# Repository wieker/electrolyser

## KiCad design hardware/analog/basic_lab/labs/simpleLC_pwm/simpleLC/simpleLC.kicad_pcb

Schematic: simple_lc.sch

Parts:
C1: C; C_Disc_D3.8mm_W2.6mm_P2.50mm
D1: D; D_DO-15_P10.16mm_Horizontal
J1: Conn_01x04_Male; PinHeader_1x04_P2.54mm_Vertical
J2: Conn_01x02_Male; PinHeader_1x02_P2.54mm_Vertical
Q1: FQP27P06; TO-220-3_Vertical
R2: R; R_Axial_DIN0207_L6.3mm_D2.5mm_P2.54mm_Vertical

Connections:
+3V3: C1.1, D1.1, J1.1, J2.2
GND: C1.2, J1.4, R2.2
unnamed: D1.2, J2.1, Q1.2 (D)
unnamed: Q1.3 (S), R2.1
din: J1.2, Q1.1 (G)

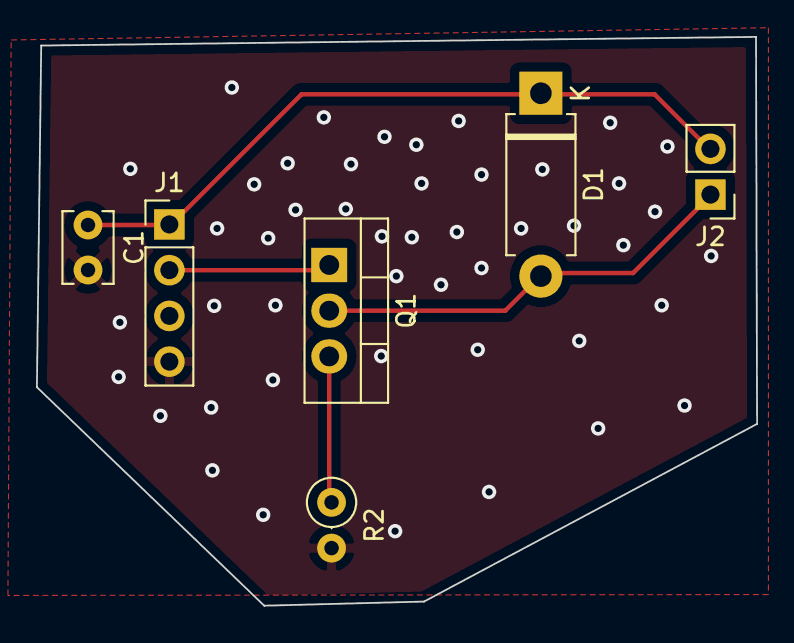
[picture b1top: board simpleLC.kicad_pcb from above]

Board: 2 copper layers, 40.0 x 31.6 mm, 6 parts (0 on the bottom side), 5 nets.

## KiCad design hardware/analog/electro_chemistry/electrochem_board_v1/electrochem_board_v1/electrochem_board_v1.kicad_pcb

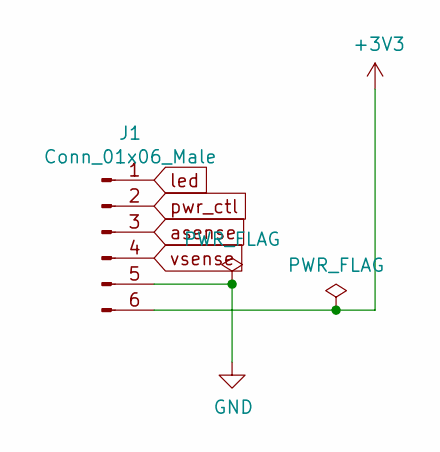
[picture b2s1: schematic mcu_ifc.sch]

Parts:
J1: Conn_01x06_Male; PinSocket_1x06_P2.54mm_Vertical

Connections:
GND: J1.5; also elsewhere on the board
asense: J1.3; also elsewhere on the board
led: J1.1; also elsewhere on the board
pwr_ctl: J1.2; also elsewhere on the board
vsense: J1.4; also elsewhere on the board

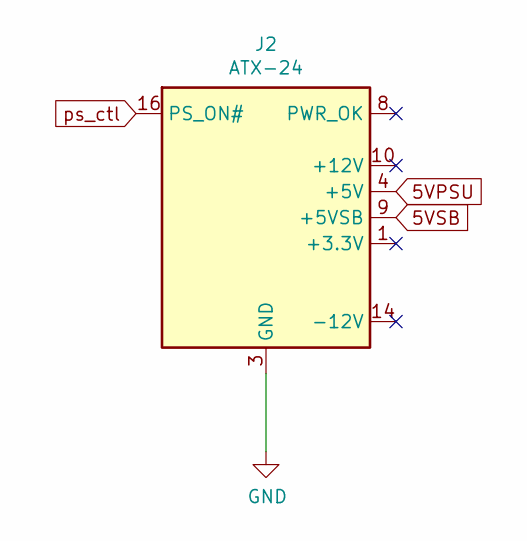
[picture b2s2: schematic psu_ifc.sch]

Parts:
J2: ATX-24; Molex_Mini-Fit_Jr_5566-24A_2x12_P4.20mm_Vertical

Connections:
5VPSU: J2.4 (+5V), J2.6 (+5V), J2.21 (+5V), J2.22 (+5V), J2.23 (+5V); also elsewhere on the board
5VSB: J2.9 (+5VSB); also elsewhere on the board
GND: J2.3 (GND), J2.5 (GND), J2.7 (GND), J2.15 (GND), J2.17 (GND), J2.18 (GND), J2.19 (GND), J2.24 (GND); also elsewhere on the board
unnamed: J2.1 (+3.3V), J2.2 (+3.3V), J2.12 (+3.3V), J2.13 (+3.3V)
unnamed: J2.10 (+12V), J2.11 (+12V)
ps_ctl: J2.16 (PS_ON#); also elsewhere on the board

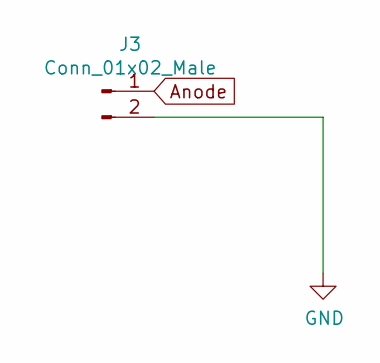
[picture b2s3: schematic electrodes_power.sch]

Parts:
J3: Conn_01x02_Male; SolderWire-1.5sqmm_1x02_P6mm_D1.7mm_OD3mm

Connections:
Anode: J3.1; also elsewhere on the board
GND: J3.2; also elsewhere on the board

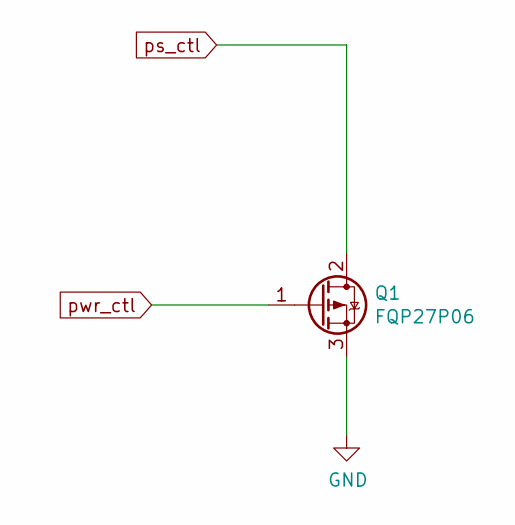
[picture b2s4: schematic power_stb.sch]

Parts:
Q1: FQP27P06; TO-220-3_Vertical

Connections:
GND: Q1.3 (S); also elsewhere on the board
ps_ctl: Q1.2 (D); also elsewhere on the board
pwr_ctl: Q1.1 (G); also elsewhere on the board

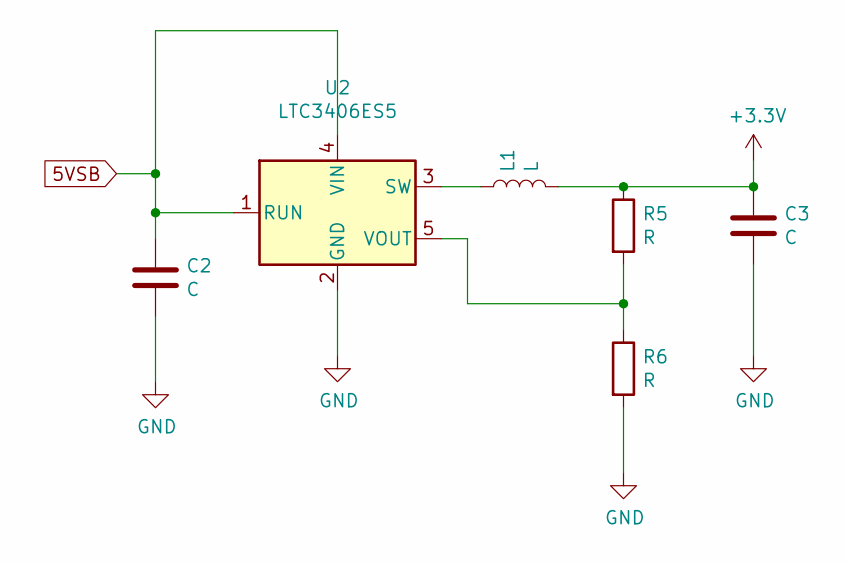
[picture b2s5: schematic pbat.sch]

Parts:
C2: C; C_0402_1005Metric
C3: C; C_0603_1608Metric
L1: L; L_1210_3225Metric
R5, R6: R; R_0402_1005Metric
U2: LTC3406ES5; TSOT-23-5

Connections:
5VSB: C2.1, U2.1 (RUN), U2.4 (VIN); also elsewhere on the board
GND: C2.2, C3.2, R6.2, U2.2 (GND); also elsewhere on the board
unnamed: L1.1, U2.3 (SW)
unnamed: R5.2, R6.1, U2.5 (VOUT)

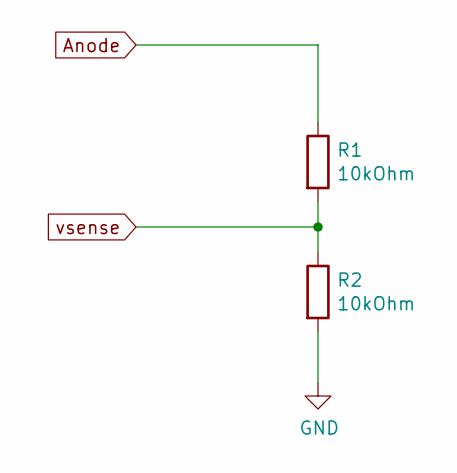
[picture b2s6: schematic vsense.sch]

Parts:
R1, R2: 10kOhm; R_0402_1005Metric

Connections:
Anode: R1.1; also elsewhere on the board
GND: R2.2; also elsewhere on the board
vsense: R1.2, R2.1; also elsewhere on the board

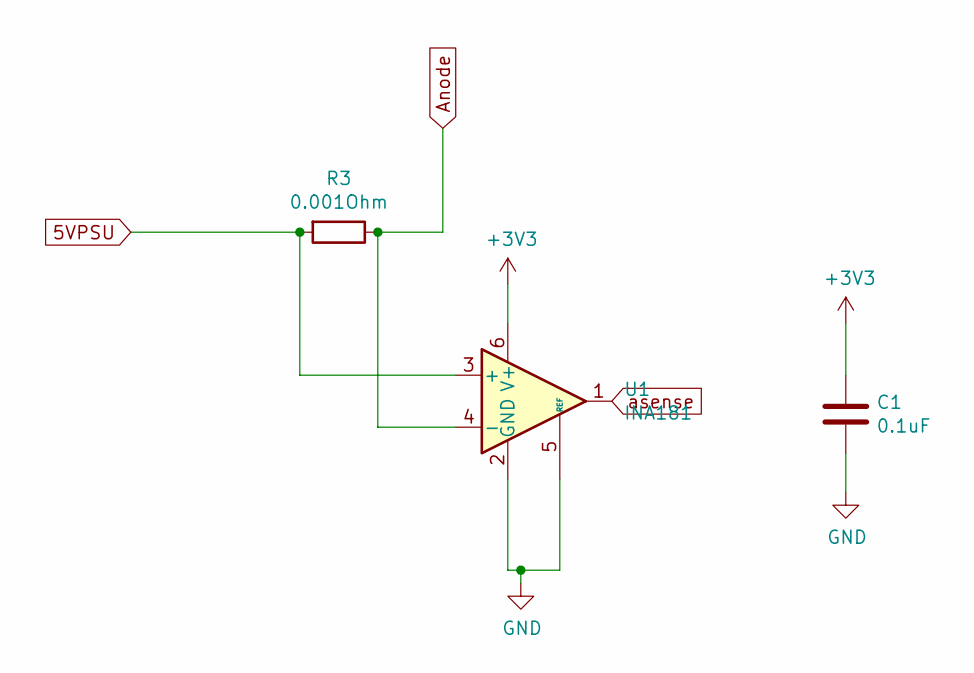
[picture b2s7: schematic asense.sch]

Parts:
C1: 0.1uF; C_0402_1005Metric
R3: 0.001Ohm; R_1206_3216Metric
U1: INA181; SOT-23-6

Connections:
5VPSU: R3.2, U1.3 (+); also elsewhere on the board
Anode: R3.1, U1.4 (-); also elsewhere on the board
GND: C1.2, U1.2 (GND), U1.5 (REF); also elsewhere on the board
asense: U1.1; also elsewhere on the board

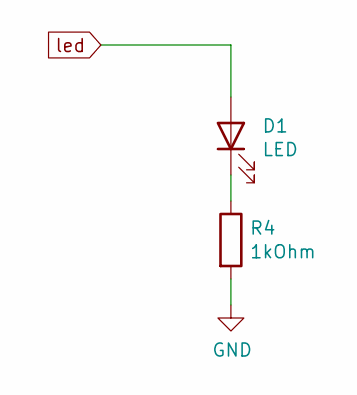
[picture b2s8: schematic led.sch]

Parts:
D1: LED; LED_1206_3216Metric
R4: 1kOhm; R_0402_1005Metric

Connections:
GND: R4.2; also elsewhere on the board
unnamed: D1.1 (K), R4.1
led: D1.2 (A); also elsewhere on the board

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
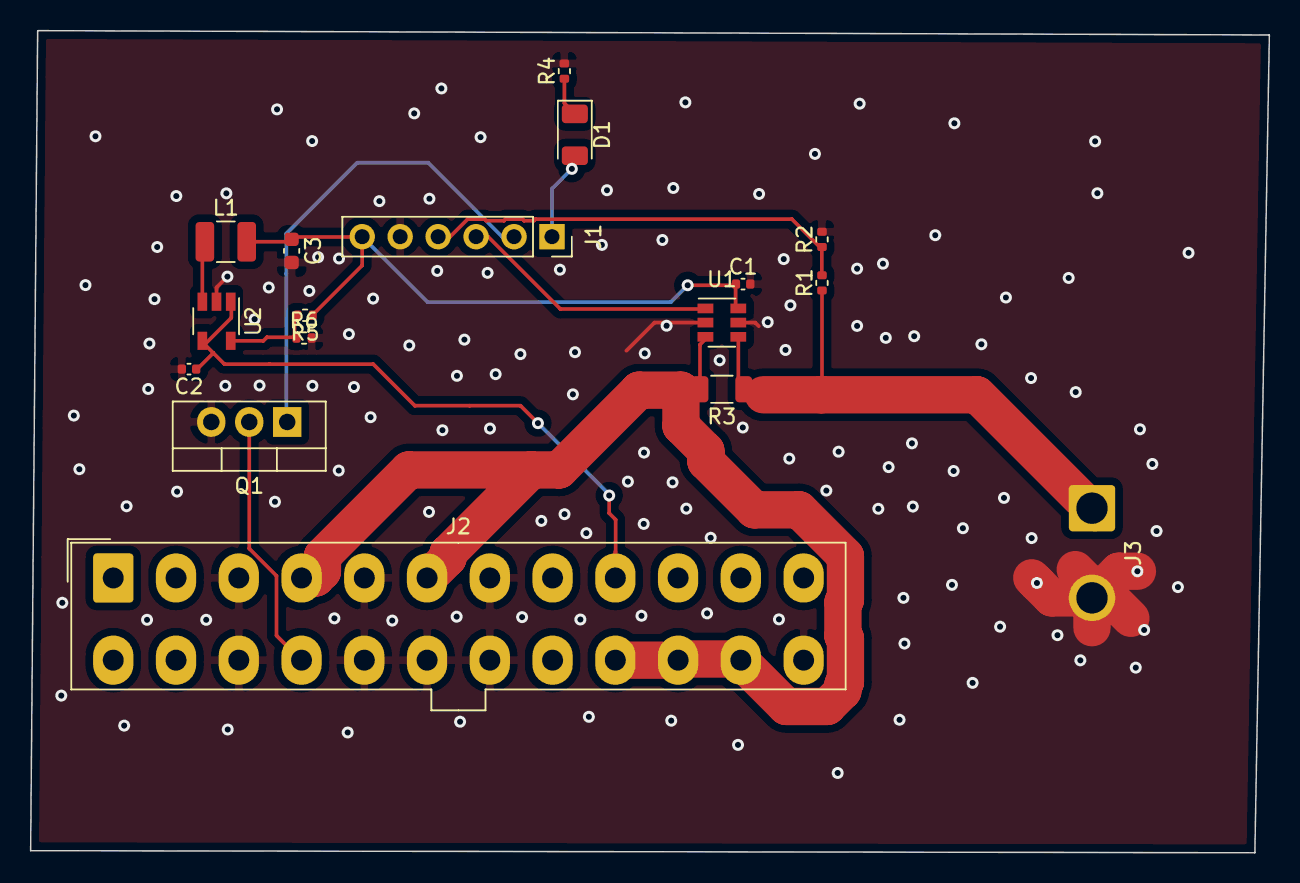
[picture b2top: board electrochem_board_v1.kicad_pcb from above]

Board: 2 copper layers, 82.9 x 55.0 mm, 17 parts (0 on the bottom side), 15 nets.

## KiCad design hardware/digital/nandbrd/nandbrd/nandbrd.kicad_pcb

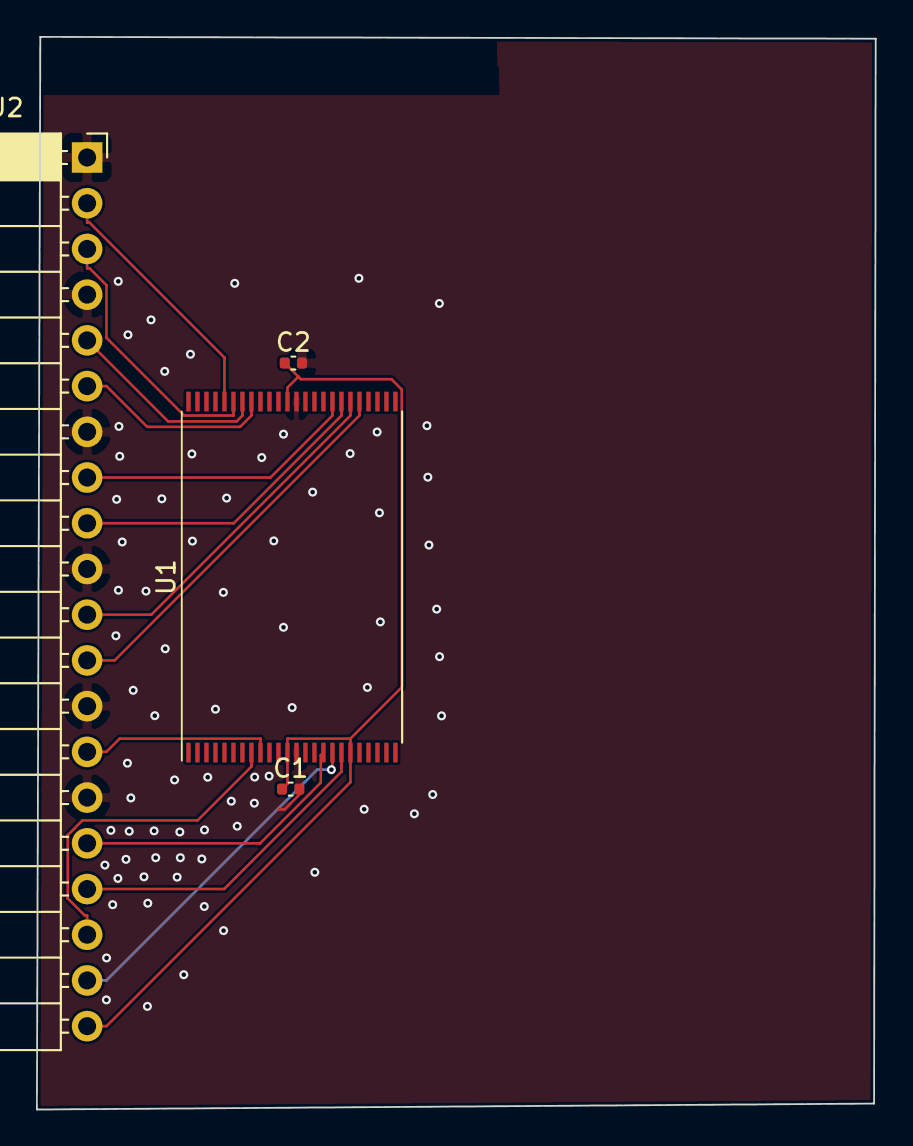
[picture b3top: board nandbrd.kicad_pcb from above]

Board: 2 copper layers, 46.6 x 59.6 mm, 4 parts (0 on the bottom side), 15 nets.

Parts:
C1: 0.1uF; C_0402_1005Metric
C2: 4.7uF; C_0402_1005Metric
J2: Conn_01x20_Male; PinSocket_1x20_P2.54mm_Horizontal
U1: MT29F1G08ABAEAWP; TSOP-I-48_18.4x12mm_P0.5mm

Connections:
ALE: J2.19, U1.17
CE: J2.14, U1.9
CLE: J2.16, U1.16
D0: J2.12, U1.29
D1: J2.11, U1.30
D2: J2.9, U1.31
D3: J2.8, U1.32
D4: J2.6, U1.41
D5: J2.5, U1.42
D6: J2.3, U1.43
D7: J2.2, U1.44
GND: C1.2, C2.2, J2.1, J2.4, J2.7, J2.10, J2.13, J2.15, U1.13, U1.36
RE: J2.18, U1.8
WE: J2.17, U1.18
WP: C1.1, C2.1, J2.20, U1.12, U1.19, U1.37

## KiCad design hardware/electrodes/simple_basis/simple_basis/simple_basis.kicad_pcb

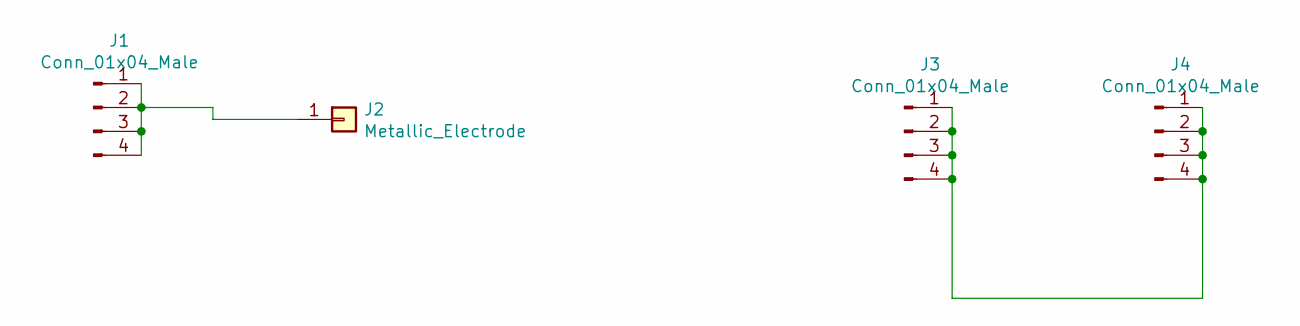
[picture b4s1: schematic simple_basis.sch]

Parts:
J1, J3, J4: Conn_01x04_Male; PinHeader_1x04_P2.54mm_Vertical
J2: Metallic_Electrode; Electrode_ThroughHole_V0.1

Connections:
unnamed: J1.1, J1.2, J1.3, J1.4, J2.1
unnamed: J3.1, J3.2, J3.3, J3.4, J4.1, J4.2, J4.3, J4.4

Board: 2 copper layers, 4 parts (0 on the bottom side), 2 nets, no tracks yet.

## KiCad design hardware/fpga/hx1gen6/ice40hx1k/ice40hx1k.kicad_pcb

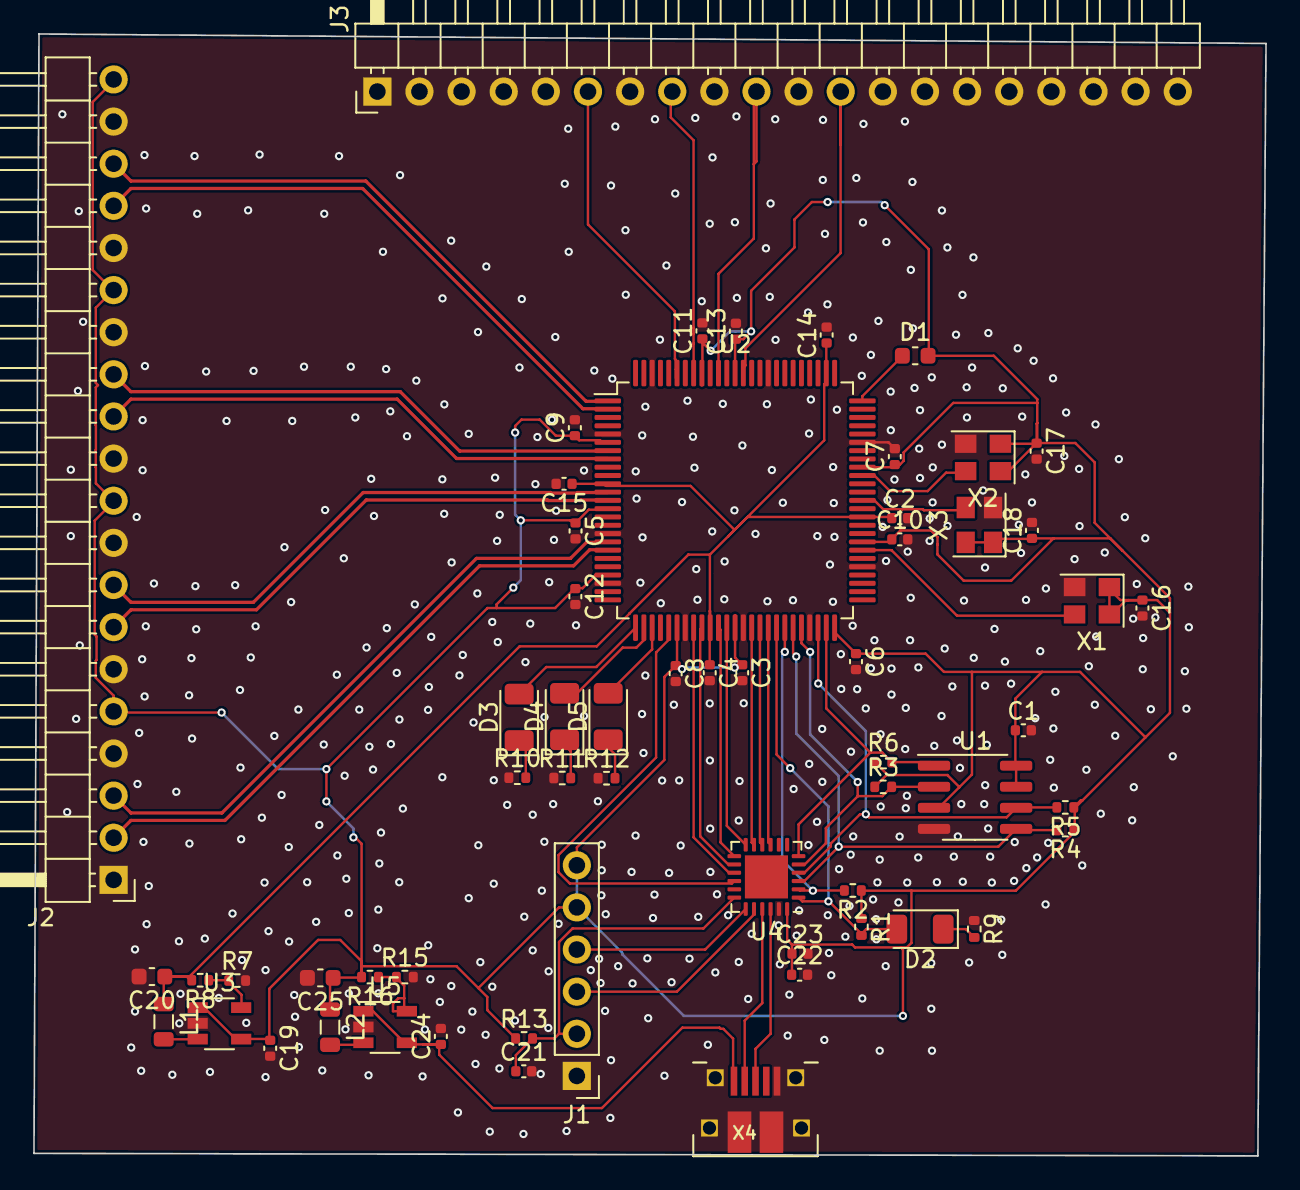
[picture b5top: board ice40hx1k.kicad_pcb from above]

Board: 2 copper layers, 74.3 x 67.6 mm, 59 parts (0 on the bottom side), 50 nets.

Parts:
C1, C2, C3, C4, C5, C6, C7, C8, C9, C10, C11, C12, C13, C14, C15, C21, C23: 0.1uF; C_0402_1005Metric
C16, C17, C18: 0.01uF; C_0402_1005Metric
C19, C22, C24: 4.7uF; C_0402_1005Metric
C20, C25: 10uF; C_0603_1608Metric
D1: CDBU05; C_0603_1608Metric
D2, D3, D4, D5: LED; LED_1206_3216Metric
J1: Conn_01x06_Male; PinHeader_1x06_P2.54mm_Vertical
J2, J3: Conn_01x20_Male; PinHeader_1x20_P2.54mm_Horizontal
L1, L2: 2.2uH; L_0805_2012Metric
R1, R2, R3, R4, R5, R6, R13: 10kOhm; R_0402_1005Metric
R7, R8, R15: 100kOhm; R_0402_1005Metric
R9, R10, R11, R12: 10kohm; R_0402_1005Metric
R16: 450kOhm; R_0402_1005Metric
U1: AT25SF081-SSHD-X; SOIC-8_3.9x4.9mm_P1.27mm
U2: ICE40HX1K-VQ100(VQFP100); LQFP-100_14x14mm_P0.5mm
U3, U5: LTC3406ES5; TSOT-23-5
U4: ATSAMD11D14A-M; QFN-24-1EP_4x4mm_P0.5mm_EP2.6x2.6mm
X1, X2, X3: ASE-10MHz; Oscillator_SMD_Abracon_ASE-4Pin_3.2x2.5mm
X4: USBFCI_10103594_MILL; FCI_10103594_MILL

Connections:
+1V2: C2.1, C4.1, C14.1, C15.1, C20.1, L1.1, R8.2, U2.11, U2.35, U2.61, U2.77
+3V3: C1.1, C3.1, C5.1, C6.1, C7.1, C8.1, C9.1, C10.1, C11.1, C12.1, C13.1, C16.1, C17.1, C18.1, C19.1, C22.1, C23.1, C25.1, D1.2, J1.5, J1.6, J2.5, J2.10, J2.15, J2.20, L2.1, R1.1, R2.1, R3.1, R4.1, R5.1, R6.1, R13.1, R16.2, U1.3, U1.7, U1.8, U2.6, U2.14, U2.22, U2.31, U2.38, U2.50, U2.58, U2.67, U2.88, U2.92, U3.1, U3.4, U4.24, X1.1, X1.4, X2.1, X2.4, X3.1, X3.4
+5V: C24.1, U5.1, U5.4, X4.VBUS
GND: C1.2, C2.2, C3.2, C4.2, C5.2, C6.2, C7.2, C8.2, C9.2, C10.2, C11.2, C12.2, C13.2, C14.2, C15.2, C16.2, C17.2, C18.2, C19.2, C20.2, C21.2, C22.2, C23.2, C24.2, C25.2, J1.1, J2.1, J2.4, J2.6, J2.9, J2.11, J2.14, J2.16, J2.19, J3.1, J3.2, J3.3, J3.4, J3.5, J3.7, J3.9, J3.11, J3.13, J3.14, J3.15, J3.16, J3.17, J3.18, J3.19, J3.20, R7.2, R9.1, R10.1, R11.1, R12.1, R15.2, U1.4, U2.5, U2.17, U2.23, U2.32, U2.39, U2.47, U2.55, U2.70, U2.84, U2.98, U3.2, U4.23, U5.2, X1.2, X2.2, X3.2, X4.BASE@1, X4.BASE@2, X4.GND, X4.SPRT@1, X4.SPRT@2, X4.SPRT@3, X4.SPRT@4
IO1_1N: J2.18, U2.1
IO1_1P: J2.17, U2.2
IO7_3N: J2.13, U2.7
IO7_3P: J2.12, U2.8
IO12_6N: J2.8, U2.12
IO12_6P: J2.7, U2.13
IO18_8N: J2.3, U2.18
IO18_8P: J2.2, U2.19
IO26: D3.2, U2.26
IO27: D4.2, U2.27
IO28: D5.2, U2.28
unnamed: D1.1, U2.75
unnamed: D2.1, R9.2
unnamed: D3.1, R10.2
unnamed: D4.1, R11.2
unnamed: D5.1, R12.2
unnamed: L1.2, U3.3
unnamed: L2.2, U5.3
unnamed: R7.1, R8.1, U3.5
unnamed: R15.1, R16.1, U5.5
unnamed: U4.21, X4.D-
unnamed: U4.22, X4.D+
cdone: D2.2, R1.2, U2.43, U4.1
clock_1: U2.66, X2.3
clock_2: U2.57, X1.3
clock_3: U2.63, X3.3
creset: R2.2, U2.44, U4.2
fpga_spi_in: R3.2, U1.2, U2.46, U4.5
fpga_spi_out: R4.2, U1.5, U2.45, U4.3
pwm_tx_1: J3.6, U2.95
pwm_tx_2: J3.8, U2.93
pwm_tx_3: J3.10, U2.90
pwm_tx_4: J3.12, U2.87
sercom1_pad0: U2.33, U4.15
sercom1_pad1: U2.30, U4.16
sercom1_pad2: U2.36, U4.13
sercom1_pad3: U2.34, U4.14
sercom2_pad0: U2.40, U4.11
sercom2_pad1: U2.37, U4.12
sercom2_pad2: U2.42, U4.9
sercom2_pad3: U2.41, U4.10
spi_clk: R5.2, U1.6, U2.48, U4.4
spi_cs: R6.2, U1.1, U2.49, U4.6
swd_clk: J1.4, U4.19
swd_io: J1.3, U4.20
swd_rst: C21.1, J1.2, R13.2, U4.18

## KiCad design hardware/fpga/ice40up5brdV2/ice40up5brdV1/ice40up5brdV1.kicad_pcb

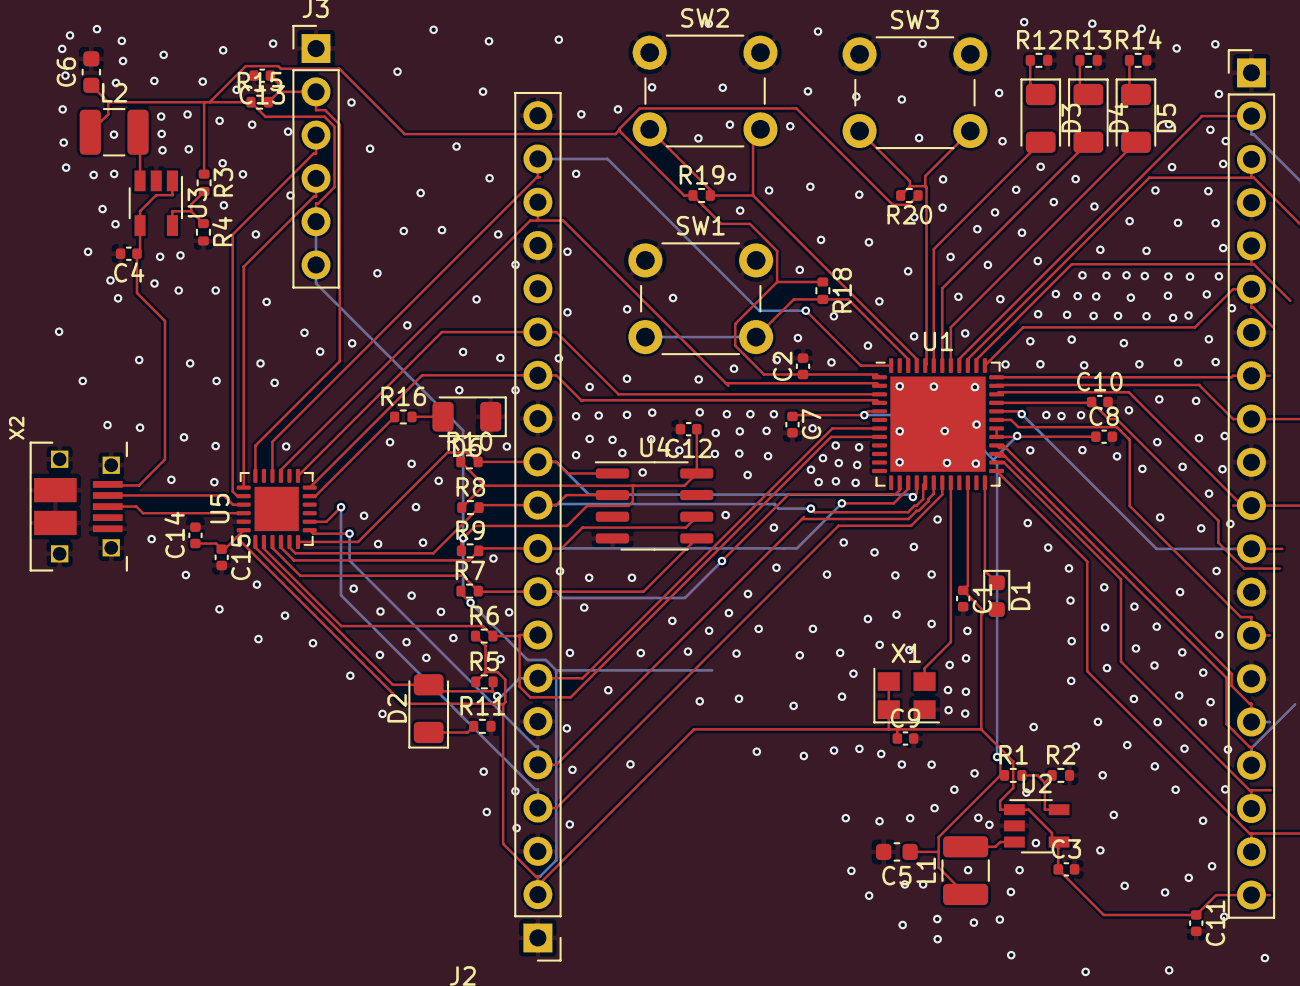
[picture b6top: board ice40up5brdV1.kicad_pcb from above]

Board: 2 copper layers, 55 parts (0 on the bottom side), 52 nets.

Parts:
C1, C2, C7, C8, C10, C11, C12, C13, C15: 0.1uF; C_0402_1005Metric
C3, C4, C14: 4.7uF; C_0402_1005Metric
C5, C6: 10uF; C_0603_1608Metric
C9: 0.01uF; C_0402_1005Metric
D1: CDBU0520; D_0603_1608Metric
D2, D3, D4, D5, D6: LED; LED_1206_3216Metric
J1: Conn_01x20_Male; PinHeader_1x20_P2.54mm_Vertical
J2: Conn_01x20_Female; PinHeader_1x20_P2.54mm_Vertical
J3: Conn_01x06_Male; PinHeader_1x06_P2.54mm_Vertical
L1, L2: L; L_1210_3225Metric
R1, R2, R4, R5, R6, R7, R8, R9, R10: 100kOhm; R_0402_1005Metric
R3: 450kOhm; R_0402_1005Metric
R11, R12, R13, R14, R18, R19, R20: R; R_0402_1005Metric
R15, R16: 10kOhm; R_0402_1005Metric
SW1, SW2, SW3: SW_Push; SW_PUSH_6mm_H8mm
U1: ICE40UP5K-SG48ITR; QFN-48-1EP_7x7mm_P0.5mm_EP5.6x5.6mm
U2, U3: LTC3406ES5; TSOT-23-5
U4: AT25SF081-SSHD-X; SOIC-8_3.9x4.9mm_P1.27mm
U5: ATSAMD11D14A-M; QFN-24-1EP_4x4mm_P0.5mm_EP2.6x2.6mm
X1: ASE-xxxMHz; Oscillator_SMD_Abracon_ASE-4Pin_3.2x2.5mm
X2: USBFCI_10103594_MILL; FCI_10103594_MILL

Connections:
+1V2: C5.1, C7.1, C8.1, L1.1, R1.1, U1.5, U1.29, U1.30
+3V3: C1.1, C2.1, C3.1, C6.1, C9.1, C10.1, C11.1, C12.1, C14.1, C15.1, D1.2, J1.20, J2.2, J3.5, J3.6, L2.1, R3.1, R5.1, R6.1, R7.1, R8.1, R9.1, R10.1, R15.1, R18.1, R19.1, R20.1, U1.1, U1.22, U1.33, U2.1, U2.4, U4.8, U5.24, X1.1, X1.4
+5V: C4.1, U3.1, U3.4, X2.VBUS
GND: C1.2, C2.2, C3.2, C4.2, C5.2, C6.2, C7.2, C8.2, C9.2, C10.2, C11.2, C12.2, C13.2, C14.2, C15.2, D6.1, J1.1, J1.4, J1.7, J1.10, J1.13, J1.15, J2.1, J2.3, J2.6, J2.13, J2.17, J2.20, J3.1, R2.2, R4.2, R11.2, R12.2, R13.2, R14.2, SW1.1, SW2.1, SW3.1, U1.49, U2.2, U3.2, U4.4, U5.23, X1.2, X2.BASE@1, X2.BASE@2, X2.GND, X2.SPRT@1, X2.SPRT@2, X2.SPRT@3, X2.SPRT@4
unnamed: D1.1, U1.24
unnamed: D2.1, R11.1
unnamed: D3.1, R12.1
unnamed: D4.1, R13.1
unnamed: D5.1, R14.1
unnamed: D6.2, R16.2
unnamed: L1.2, U2.3
unnamed: L2.2, U3.3
unnamed: R1.2, R2.1, U2.5
unnamed: R3.2, R4.1, U3.5
unnamed: U5.21, X2.D-
unnamed: U5.22, X2.D+
a1: J2.14, U1.4, U5.12
a2: J2.18, U1.2, U5.15
ale: J1.19, U1.25
b1: J2.15, U1.3, U5.13
b2: J2.19, U1.48, U5.16
btn1: R18.2, SW1.2, U1.46
btn2: R19.2, SW2.2, U1.45
btn3: R20.2, SW3.2, U1.44
cdone: D2.2, J2.7, R5.2, U1.7, U5.1
ce: J1.14, U1.31
cle: J1.16, U1.28
clk: U1.20, X1.3
creset: J2.8, R6.2, U1.8, U5.2
d0: J1.12, U1.32
d1: J1.11, U1.34
d2: J1.9, U1.35
d3: J1.8, U1.36
d4: J1.6, U1.37
d5: J1.5, U1.38
d6: J1.3, U1.39
d7: J1.2, U1.40
fpga_rx: J2.5, U1.18, U5.7
fpga_tx: J2.4, U1.19, U5.8
l1: D5.2, U1.41
l2: D4.2, U1.42
l3: D3.2, U1.43
led_mcu: R16.1, U5.11
miso: J2.11, R8.2, U1.17, U4.2, U5.5
mosi: J2.9, R7.2, U1.14, U4.5, U5.3
re: J1.18, U1.26
sck: J2.10, R9.2, U1.15, U4.6, U5.4
ss: J2.12, R10.2, U1.16, U4.1, U5.6
swd_clk: J3.4, U5.19
swd_io: J3.3, U5.20
swd_rst: C13.1, J3.2, R15.2, U5.18
we: J1.17, U1.27
